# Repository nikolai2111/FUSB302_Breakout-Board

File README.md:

# FUSB302_Breakout-Board <!-- omit from toc -->
## Content <!-- omit from toc -->
- [1. Description](#1-description)
- [2. Folder structure](#2-folder-structure)
- [3. Usage](#3-usage)
- [4. License](#4-license)

## 1. Description
This is a very simple and low level breakout board for the FUSB302B Programmable USB Type-C Controller chip. Actually it's a breakout board for the WQFN14 footprint with only the footprint on it, nothing else.  The project was implemented with KiCAD, as single board or as a panel. It contains ready-to-use Gerber files for both, the single board and the panel (5x5 pcs.). For PCBWay Project click [here](https://www.pcbway.com/project/shareproject/FUSB302_Breakout_Board_Panel_5x5_pcs_0b5aa18a.html).

## 2. Folder structure
TBC

## 3. Usage
Add instructions and examples here.

## 4. License
The hardware and its documentation is licensed under the CERN-OHL-P licence, which can be found [here](LICENSE).

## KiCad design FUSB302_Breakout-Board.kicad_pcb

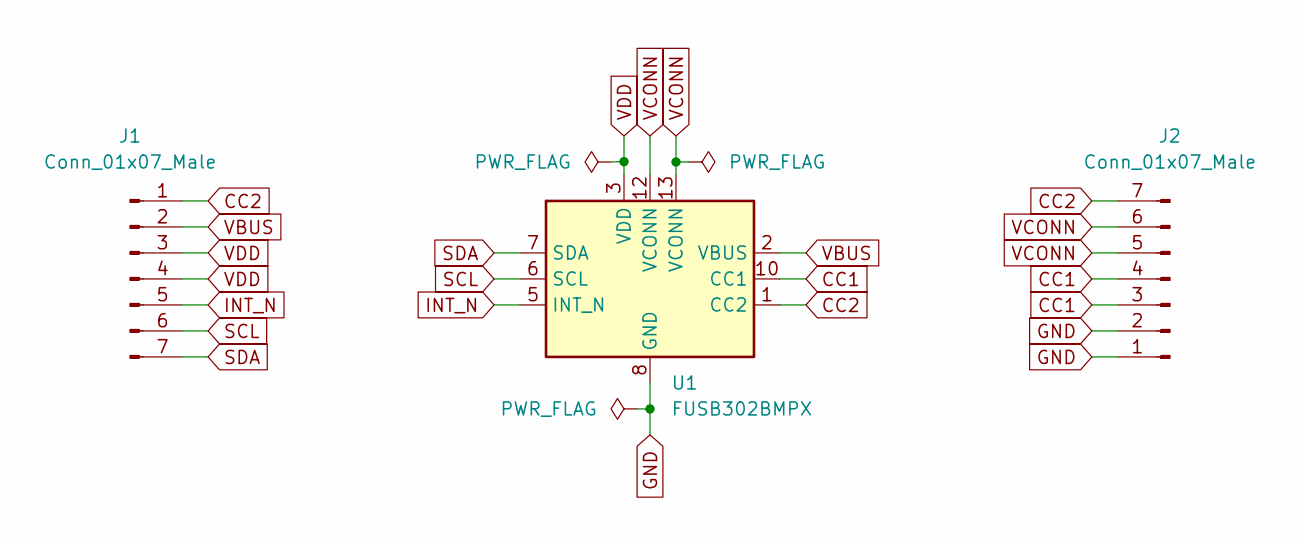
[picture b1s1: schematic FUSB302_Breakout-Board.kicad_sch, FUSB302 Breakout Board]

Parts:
J1: Conn_01x07_Male
J2: Conn_01x07_Male; PinHeader_1x07_P2.54mm_Vertical
U1: FUSB302BMPX; WQFN-14-1EP_2.5x2.5mm_P0.5mm_EP1.45x1.45mm

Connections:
CC1: J2.3, J2.4, U1.10 (CC1), U1.11 (CC1)
CC2: J1.1, J2.7, U1.1 (CC2), U1.14 (CC2)
GND: J2.1, J2.2, U1.8 (GND), U1.9 (GND), U1.15 (GND)
INT_N: J1.5, U1.5 (INT_N)
SCL: J1.6, U1.6 (SCL)
SDA: J1.7, U1.7 (SDA)
VBUS: J1.2, U1.2 (VBUS)
VCONN: J2.5, J2.6, U1.12 (VCONN), U1.13 (VCONN)
VDD: J1.3, J1.4, U1.3 (VDD), U1.4 (VDD)

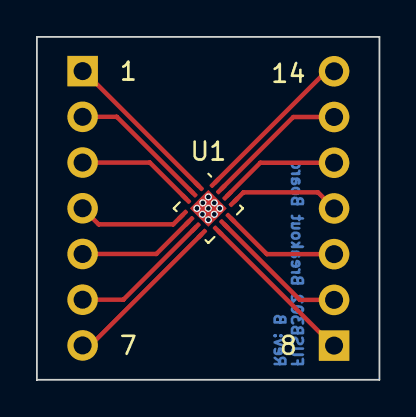
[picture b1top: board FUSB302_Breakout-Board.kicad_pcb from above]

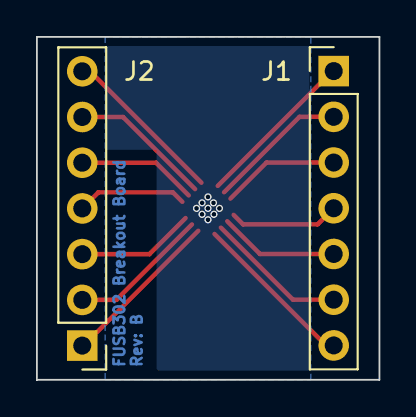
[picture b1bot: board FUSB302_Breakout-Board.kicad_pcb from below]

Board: 2 copper layers, 19.0 x 19.0 mm, 3 parts (2 on the bottom side), 9 nets.

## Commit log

2023-03-03 Add: CERN-OHL-P license
2023-03-03 Mod: README Used my default README file structure and filled it out
2023-03-03 Add: KiCAD Project with Schematic, PCB, Panel (5x5 pcs.) and export files
2023-03-03 Mod: .gitignore, ignore backup and build files
2023-03-03 Del: Removed unused files
2023-03-03 Add: Gerber files as a archive Mod: Description in README
2023-03-04 Mod: PCB, added vias to filled zone on the bottom for a better heat path Mod: Panel, with new pcb Mod: Exports
2023-03-04 Mod: Documentation in README file and updated pcb top picture
2023-03-04 Mod: Bottom solder mask, pasted logo in to it and exported the pcb with the v-cuts
2023-03-04 Mod: Fixed problem with bottom filled zone
2023-03-06 Mod: Corrected trace to first pin, added Rev. and Prj. to the bottom solder mask
2023-03-06 Mod: Layout export, corrected issue date
2023-03-07 Mod: Updated the project name and revision to be on the copper layer now
2023-03-07 Mod: The project name string

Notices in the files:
FUSB302_Breakout-Board.kicad_sch:
License: CERN-OHL-P
